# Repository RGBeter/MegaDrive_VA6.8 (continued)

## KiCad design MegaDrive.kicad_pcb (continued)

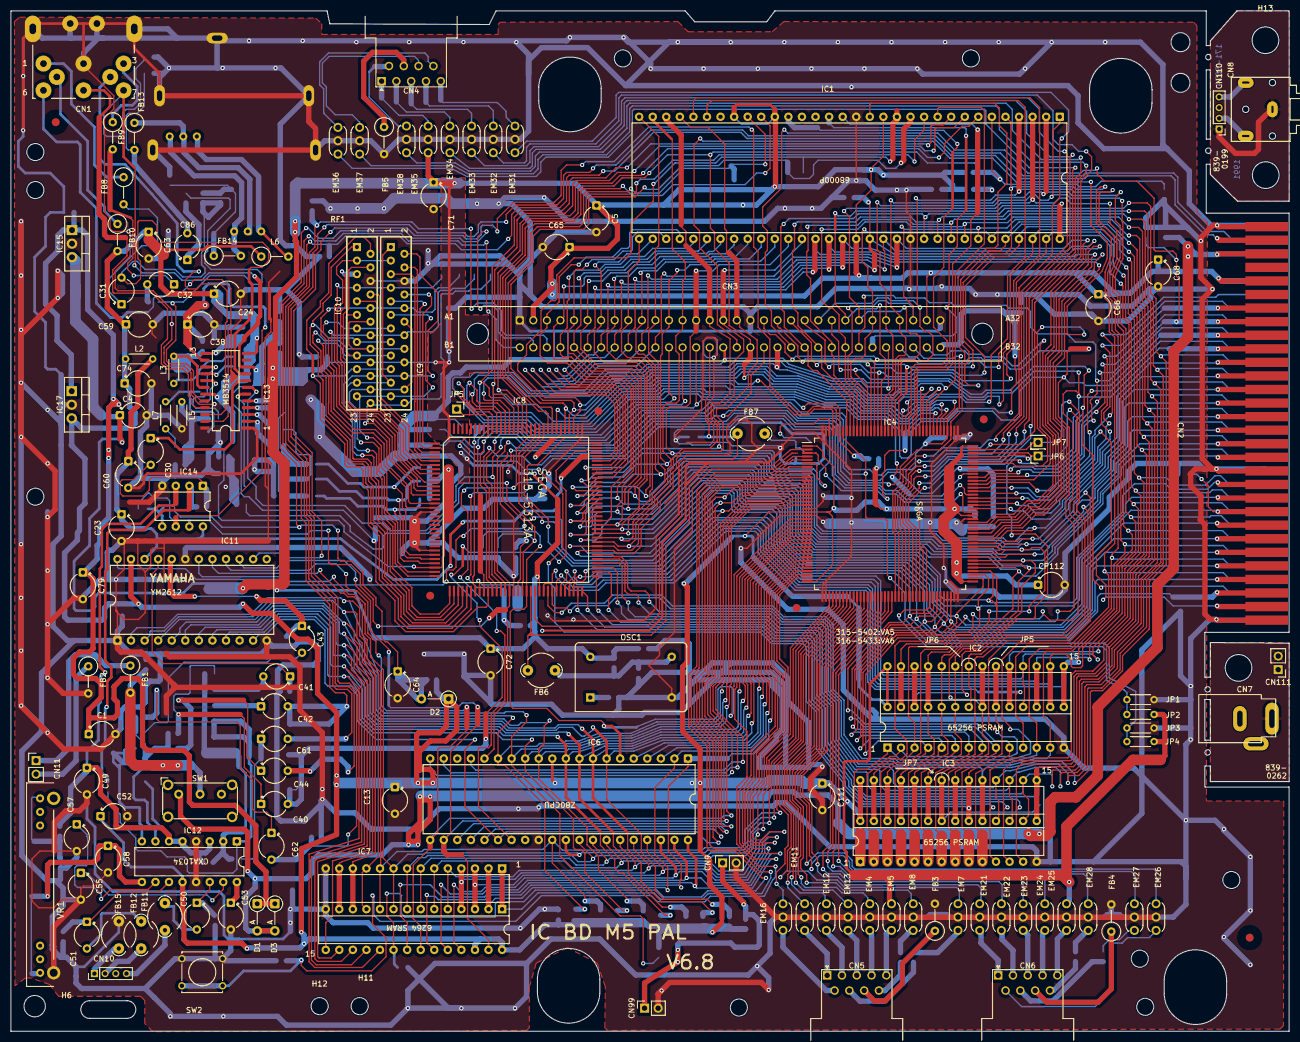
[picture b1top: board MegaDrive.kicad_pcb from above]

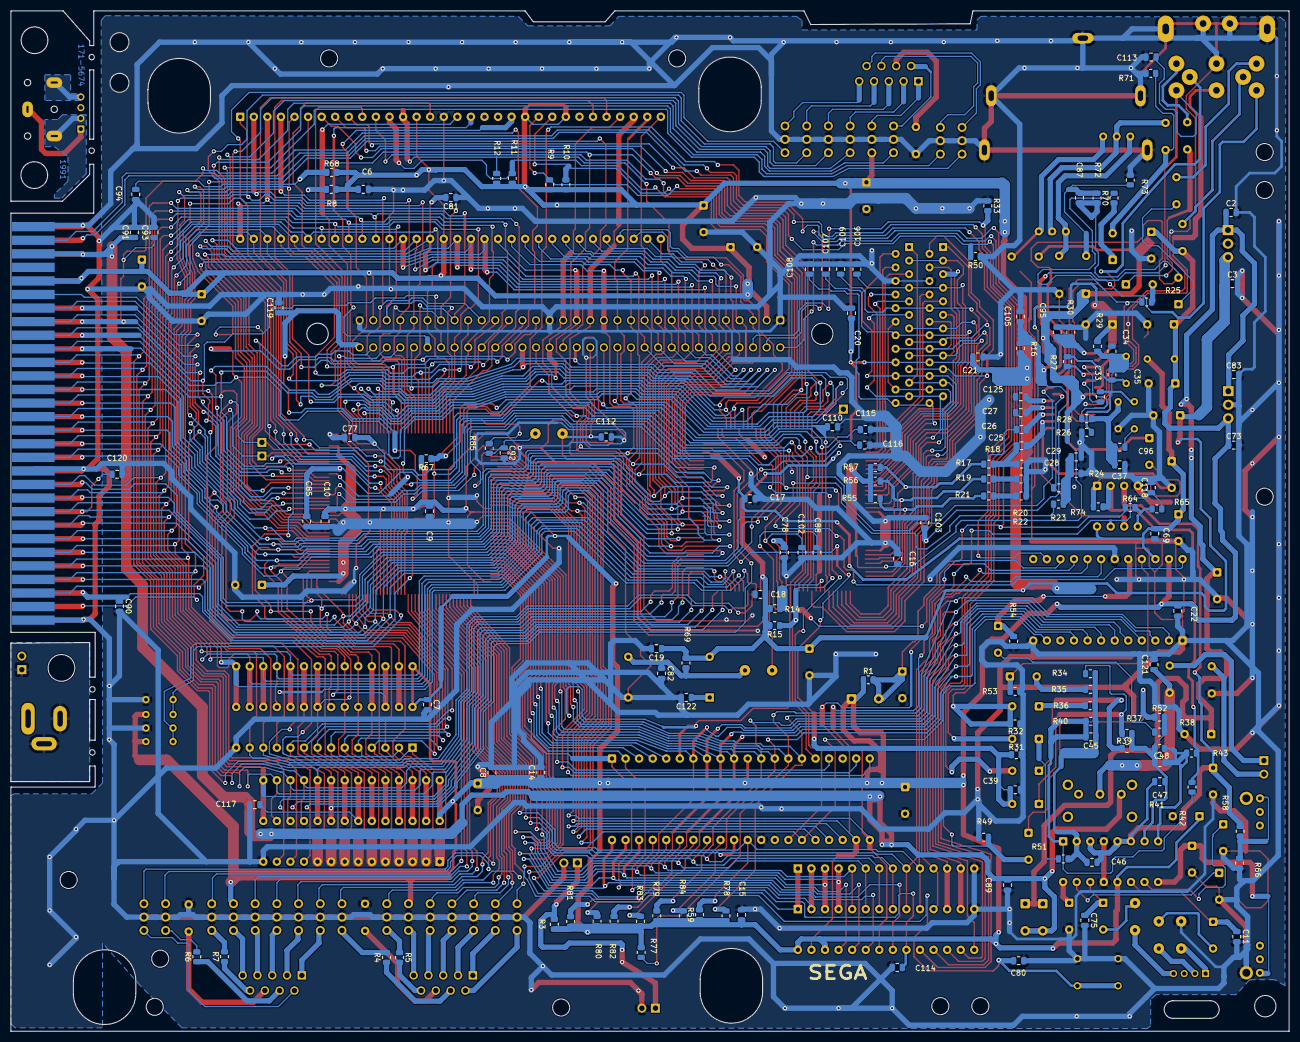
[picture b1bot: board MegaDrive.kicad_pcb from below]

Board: 2 copper layers, 239.3 x 191.0 mm, 292 parts (144 on the bottom side), 299 nets.
